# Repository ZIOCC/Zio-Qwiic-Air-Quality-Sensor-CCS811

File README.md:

# Zio Qwiic Air Quality Sensor (CCS811)

> This product can be available for purchase [here](https://www.smart-prototyping.com/Zio-Qwiic-Air-Quality-Sensor-CCS811).

#### Description

The Zio Qwiic Air Quality features a CCS811 sensor from AMS, it’s a very small size gas sensor and it can detect a wide range of Volatile Organic Compounds (VOCs) for indoor air quality monitoring. 
 
This sensor can measure

* eCO2 (equivalent calculated carbon-dioxide), from 400 to 8192 ppm (parts per million)
* VOC (Total Volatile Organic Compound, from 0 to 1187 ppb (parts per billion)
* Ambient temperature (optional), it can help compensate the readings. 

Likewise all VOC/ gas sensors, the sensor has to be calibrated before use. Per AMS recommendation, the sensor has to run 48 hours the first time of use. Then 20 minutes on preferred mode every time it is used.

The CCS811 has a configurable interrupt pin, it can fire when a conversion is ready as well as when a reading crosses a user-settable threshold. It also has ability to take measurements supporting multiple drive modes to take measurements every 250 milliseconds, 1, 10 and 60 seconds.

Like other Zio Qwiic boards, it incorporates the Qwiic connector for it’s convenient and practical setup. Although, we also incorporated the breakout pins on the board to be able to use it on a breadboard.

#### Specification

* Operation Voltage: 3.3V
* Interface: I2C (address 0x5A and 0x5B)
* Dimensions: 25.5 x 26.6mm
* Weight:1.7g

#### Links

* [PCB Source File and Schematic](https://github.com/ZIOCC/Zio-Qwiic-Air-Quality-Sensor-CCS811)
* [CCS811 Datasheet](https://ams.com/documents/20143/36005/CCS811_DS000459_6-00.pdf/)
* [Sparkfun CCS811 Library](https://github.com/sparkfun/SparkFun_CCS811_Arduino_Library)
* [Adafruit CCS811 Library](https://github.com/adafruit/Adafruit_CCS811)

> ###### About Zio
> Zio is a new line of open sourced, compact, and grid layout boards, fully integrated for Arduino and Qwiic ecosystem. Designed ideally for wearables, robotics, small-space limitations or other on the go projects. Check out other awesome Zio products [here](https://www.smart-prototyping.com/Zio).

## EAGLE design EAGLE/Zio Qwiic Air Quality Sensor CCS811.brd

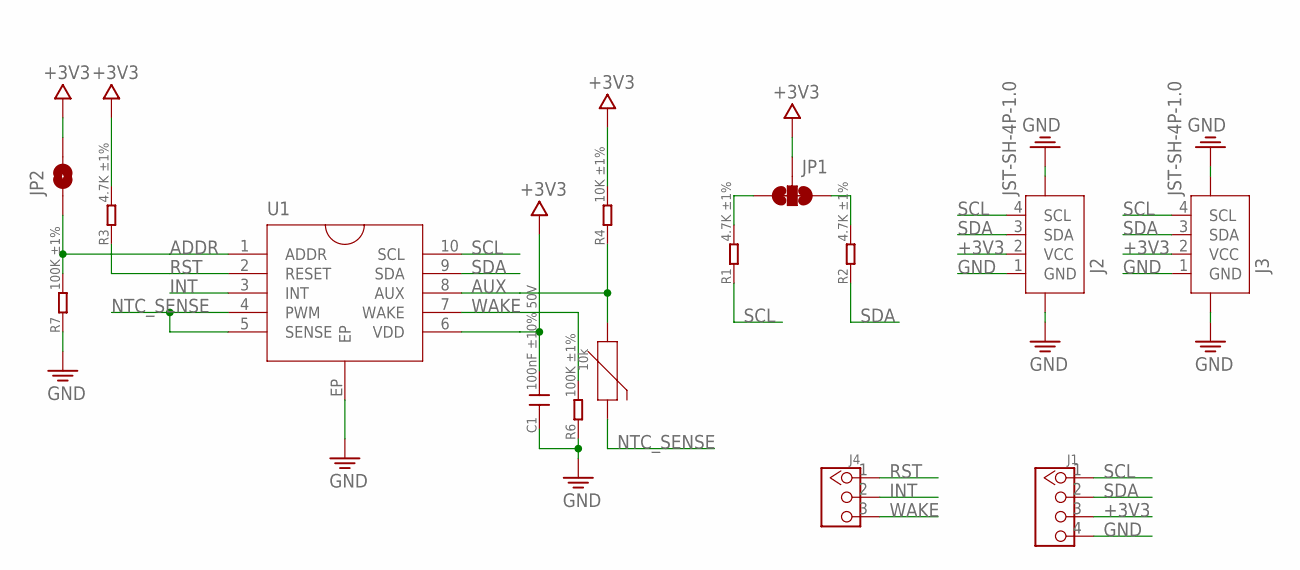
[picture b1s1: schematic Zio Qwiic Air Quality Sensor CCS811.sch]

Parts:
C1: 100nF ±10% 50V; C0603
J1: HEADER-4P-60/35MIL; 4P-65/35MIL
J2, J3: JST-SH-4P-1.0; JST-SH-4P
J4: HEADER-3P-2.54; 3P-2.54
JP1: SMT-JUMPER_3_2-NC_TRACE
JP2: JUMPER-SMT_2_NC_PASTE_NOCREM; SMT-JUMPER_2_NC_PASTE_SILK_NOCREM
R1, R2, R3: 4.7K ±1%; R0603
R4: 10K ±1%; R0603
R5: 10k; NTC
R6, R7: 100K ±1%; R0603
U1: CCS811B; LGA10

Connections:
+3V3: C1.2, J1.3, J2.2 (VCC), J3.2 (VCC), JP1.2, JP2.2, R3.2, R4.2, U1.6 (VDD)
ADDR: JP2.1, R7.2, U1.1 (ADDR)
AUX: R4.1, R5.2, U1.8 (AUX)
GND: C1.1, J1.4, J2.1 (GND), J2.NC1 (5), J2.NC2 (6), J3.1 (GND), J3.NC1 (5), J3.NC2 (6), R6.1, R7.1, U1.EP
INT: J4.2, U1.3 (INT)
unnamed: JP1.3, R1.2
unnamed: JP1.1, R2.2
NTC_SENSE: R5.1, U1.4 (PWM), U1.5 (SENSE)
RST: J4.1, R3.1, U1.2 (RESET)
SCL: J1.1, J2.4 (SCL), J3.4 (SCL), R1.1, U1.10 (SCL)
SDA: J1.2, J2.3 (SDA), J3.3 (SDA), R2.1, U1.9 (SDA)
WAKE: J4.3, R6.2, U1.7 (WAKE)

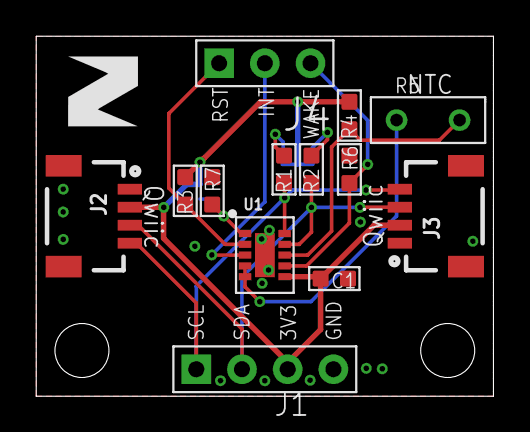
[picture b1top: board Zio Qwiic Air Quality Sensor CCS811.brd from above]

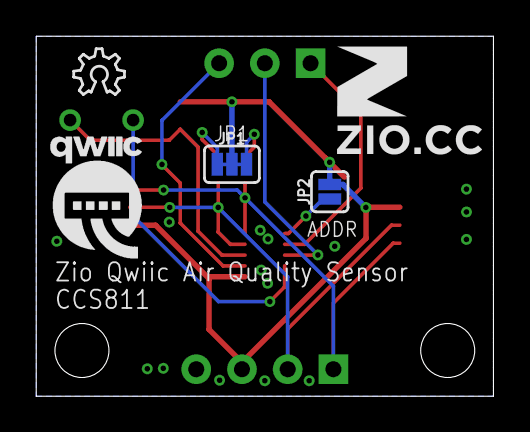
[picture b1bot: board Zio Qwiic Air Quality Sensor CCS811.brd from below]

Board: 2 copper layers, 25.4 x 20.0 mm, 19 parts (5 on the bottom side), 12 nets.

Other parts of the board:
U$6, U$9: 6MM
U$7: QWIIC-LOGO-MEDIUM
U$8: OSHW_6X100_NOTEXT
